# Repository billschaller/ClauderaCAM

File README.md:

# ClauderaCAM

Claude-drivable 2.5D heightmap CAM for the Makera Carvera Air.
STL relief → rough / semi / finish / cutout → **physical stock-simulation
verification** → live 3D viewer → .nc. Built from the exact code that cut
the brass Mango coin, then hardened by a 42-agent adversarial review whose
35 confirmed findings are each either fixed or a named check (see DESIGN.md
"2026-07-28: adversarial review & hardening"). A second lane mills PCBs
from KiCad gerbers through the same gate (see **The PCB lane** below).

## Setup

```sh
python3 -m venv .venv
.venv/bin/python -m pip install -e .          # pure-python (works everywhere)
.venv/bin/python -m pip install ./kernel      # optional Rust kernel (~10-50x
                                              # faster verify; needs cargo)
```

The two kernels are parity-locked (`tests/kernel_parity.py`): bit-exact
stock, epsilon-exact measurements. The Python one is the semantic reference.

## MCP (primary interface)

`.mcp.json` in this repo registers the server for Claude Code sessions
started here. From elsewhere:

```sh
claude mcp add --scope user clauderacam -- \
  <repo>/.venv/bin/python -m clauderacam.mcp_server
```

Tools: `load_job`, `generate`, `verify`, `preview`, `view` (opens the
job as a session in the live viewer, starting a server only if none is
running), `sessions` (lists open sessions). There is deliberately no
upload tool — .nc files reach the machine only by hand.

The viewer is a stage-aware, multi-session inspection app. One server
holds many sessions — one per open job file — and every process joins
it: the MCP, the CLI and any number of browser tabs land on the same
server via a discovery file, so a change Claude pushes appears in the
watching browser within a second. Sessions are keyed by job path, so
opening a file that is already open joins its session (that's the
collaboration model). In the browser: a session list with verdict
badges and a job-file picker (opening verifies in the background; the
browser never generates or edits — job changes are Claude's); per
session, the program's logical operations (recovered from the .nc bytes
themselves) as a selectable list with per-stage time estimates —
selecting one shows the simulated stock as it will exist after that
operation with the material that stage removes highlighted — plus a
stage-detail card (removed volume, tool contact, windowed chip load and
cutting power, each drawn as a utilization bar against its limit), the
tool library with the active stage's tool marked, and the full check
list. Claude runs the job; the viewer exists so a human — including a
CAM expert — can audit it. Each session offers a **download** of its
program — serving the exact bytes that were verified (stored at push
time; a later regenerate can never hand out unverified toolpaths under
a displayed PASS), with an explicit are-you-sure on anything not
cleared for metal. Downloading to a human hand is the Article VII
workflow: the file still reaches the machine only by that hand.

## CLI

```sh
.venv/bin/clauderacam all jobs/mango.toml       # generate + verify + preview
.venv/bin/clauderacam view jobs/mango.toml      # open in the live viewer at
                                                # :8323 (joins a running
                                                # server, else serves)
.venv/bin/clauderacam serve                     # empty viewer server; open
                                                # job files from the browser
```

## The rule

**Nothing goes to the machine without `verify` returning PASS.** The verifier
strictly parses the program (anything it cannot model — unknown tools, arcs,
modal G-less lines — is fatal, never skipped), carves every move into
virtual stock, and checks:

- *geometry (simulation facts):* rapids (lateral and descending), true
  per-move tool contact for every tool (footprint max vs move-start stock,
  limits calibrated to metal evidence), shank/holder clearance against
  standing stock, depth vs stock bottom, gouging below the target surface,
  surface completeness, cutout sever-through, the fixture keep-out zone,
  and the spindle-state dialect (M5 before M6, dwell after M3)
- *cutting physics (model verdicts, provenance-annotated in physics.py):*
  per-material sustained chip load and spindle power over 0.25s windows,
  rubbing (starvation feed), plunge rate, machine feed caps, a sustained-
  power heat proxy, and an enclosed-chip gumming proxy — materials carry
  specific cutting energy, chip-load floors and evacuation limits; tools
  carry flutes, flute length and shank geometry; the machine model is the
  Carvera Air's 200W / 13k RPM spindle

`tests/negative_suite.py` proves the gate can fail: 24 distilled hazards —
slams, stalls, rubbing, gumming, shank crashes, rapid plunges, arcs in
disguise — that must each be caught. `tests/stage_model.py` proves the
per-stage model tells the truth: stage snapshots partition the carve
bit-exactly and per-stage stats are measured, not inferred.

## Golden test

```sh
.venv/bin/python tests/golden_mango.py
```

Regenerates the mango job (`assets/mango-coin-d52.stl` — yes, that's a real
cat) and asserts byte-identical toolpaths against the G-code in
`tests/golden/` that cut the physical coin, then verifies the assembled
program. Run it after touching anything in `ops/`, `engine.py`, or
`heightmap.py`.

## Reference suite

```sh
.venv/bin/python tests/reference_suite.py
```

`assets/generate_references.py` synthesizes four deterministic shapes, each
paired with a job in `jobs/` that stresses a different hazard:

| job | exercises |
|---|---|
| `terraces` | layered-rough terracing on 0.22mm steps, simplify on flats, cutout with tabs |
| `dome` | 2mm flat rough (smaller tool = relaxed slope budget), two-ball finish chain, no cutout |
| `ripple` | 1mm ball finishing **directly** after rough — legal only because every slope is inside the engagement budget |
| `pocketfield` | graduated feature access by tool BODY (Ø7 down to 1.3mm slots) — honestly annotated: the shallow features are bottomed by the 2mm ball's contact circle; true tool exclusion awaits depth-stepped clearing |

Together with mango these cover the supported tool set: flat 3.175, flat 2.0,
ball 2.0, ball 1.0, plus twist drills for registration holes — the
geometries validated by cut metal. V-bits and tapered ball noses need a
conical offset model plus a real-world tip engagement limit, so they are
roadmap, not shipped guesses.

## Two-sided (pin-and-flip) jobs

One TOML with `[twosided]`, `[pins]` and per-side op lists describes a
coin machined on BOTH faces: side 1 cuts the front art plus a minimal
moat, then spot-faces and peck-drills registration holes through the
stock into the spoilboard — same setup, so the holes are coaxial by
construction. Flip the blank onto dowel pins (layout must be symmetric
under the configured flip axis — enforced), and side 2 cuts the back art
and the tabbed cutout. Two .nc programs come out; each verifies through
the same gate, and the back side is additionally checked against the
carried, flipped front stock: punch-through into the front art, sever
against the actual material bottom, a continuous tab bridge from coin to
skeleton, and pin keep-out. The cutout's `tab_top` is derived from the
carried front floor to hit a target `tab_bridge` thickness (hand-written
values are refused — the first cut coin's hand-picked tab_top made
0.24mm tabs that snapped too thin). `jobs/twoside-ref.toml` +
`tests/twosided_suite.py` are the executable spec, negatives included.

## The PCB lane

Gerbers + Excellon in, verified Carvera programs out: isolation-milled
PCBs through the same gate. A `[pcb]` TOML names a KiCad export
directory and parameterizes the operator's six-phase chain — cut traces
(0.2mm vee, a multi-pass ladder so gaps too wide for one pass and too
narrow for the clearing tool still come out copper-free) → clear copper
→ solder mask *(operator: squeegee + UV cure)* → silkscreen (455nm
laser onto the cured mask) → scrub mask off pads (spring tool) →
drills + edge cut. FlatCAM (a pinned headless
fork) runs as the **geometry engine only**: its per-phase output is
strictly parsed and re-emitted through `emit.py`, so every shipped byte
obeys the house dialect (the laser program has its own — one `M321`,
then a mandatory `G0 Z0` defocus, dose-ceilinged `M3 S`). Verification
never trusts the generator: gerbv rasterizes the same gerbers through
an unrelated parser lineage, and the gate measures the assembled
programs against those maps — iso containment *and* coverage, a
residual-copper law on the simulated carve (no bridging sliver survives
between what isolation reaches and what clearing owns — a loupe-found
incident), clearing margins, scrub laps inside pad copper, pad
scrubbability, thermal-relief spoke delivery, silk clearance and stroke
metrics, the exact Excellon hole schedule, cutout ride + tab census,
and true sheet stock simulation for the milling programs
(`guides/pcb-dfm-notes.md` translates the big fab houses' hand-solder
DFM rules into this milled lane's numbers). Double-sided boards compose
`[pcb]` + `[twosided]`: per-side phase tables, both machine frames
derived from the one Edge.Cuts, registration pins under the coin lane's
pins law, both-side annular-ring and flip-concentricity checks for
hand-soldered wire vias, and a side-2 scrub generator that laps
drilled pads annularly instead of driving the spring tip across open
holes. Board contracts — plus each board's assembly map, companion
sheet and machine-side tool pull-list — live in `boards/`, golden
assets in `tests/golden_pcb/`; the viewer opens a `[pcb]` job as one
session per
program, with 2D overlays for the non-carving stages and the
operator's run-sheet card. FlatCAM and gerbv are external optional
binaries (like the Rust kernel): the blessed goldens verify without
them and the suites skip loudly.

## The tool crib

`jobs/inventory.toml` is the machine's physical tool inventory. A job may
only use tools that match an entry — type, diameter, shank, flutes,
reach, quantity on hand — and refuses to **load** otherwise (Article XI).
Geometry in the crib is measured or catalog-sourced, never guessed; a
tool with an unknown dimension is absent, and the resulting refusal is
the feature.

## Project law

`CLAUDE.md` is the constitution: the verification gate, the golden-test
contract, and the incident-traced safety rules. Read it before contributing —
human or model.

## License & credits

MIT (see LICENSE). Vendors [three.js](https://threejs.org) r160 (MIT) for the
viewer. Named for Claude + Carvera: designed and written by
[Claude Code](https://claude.com/claude-code) working alongside a human
machinist, and proven by cutting real metal before it was ever a package.

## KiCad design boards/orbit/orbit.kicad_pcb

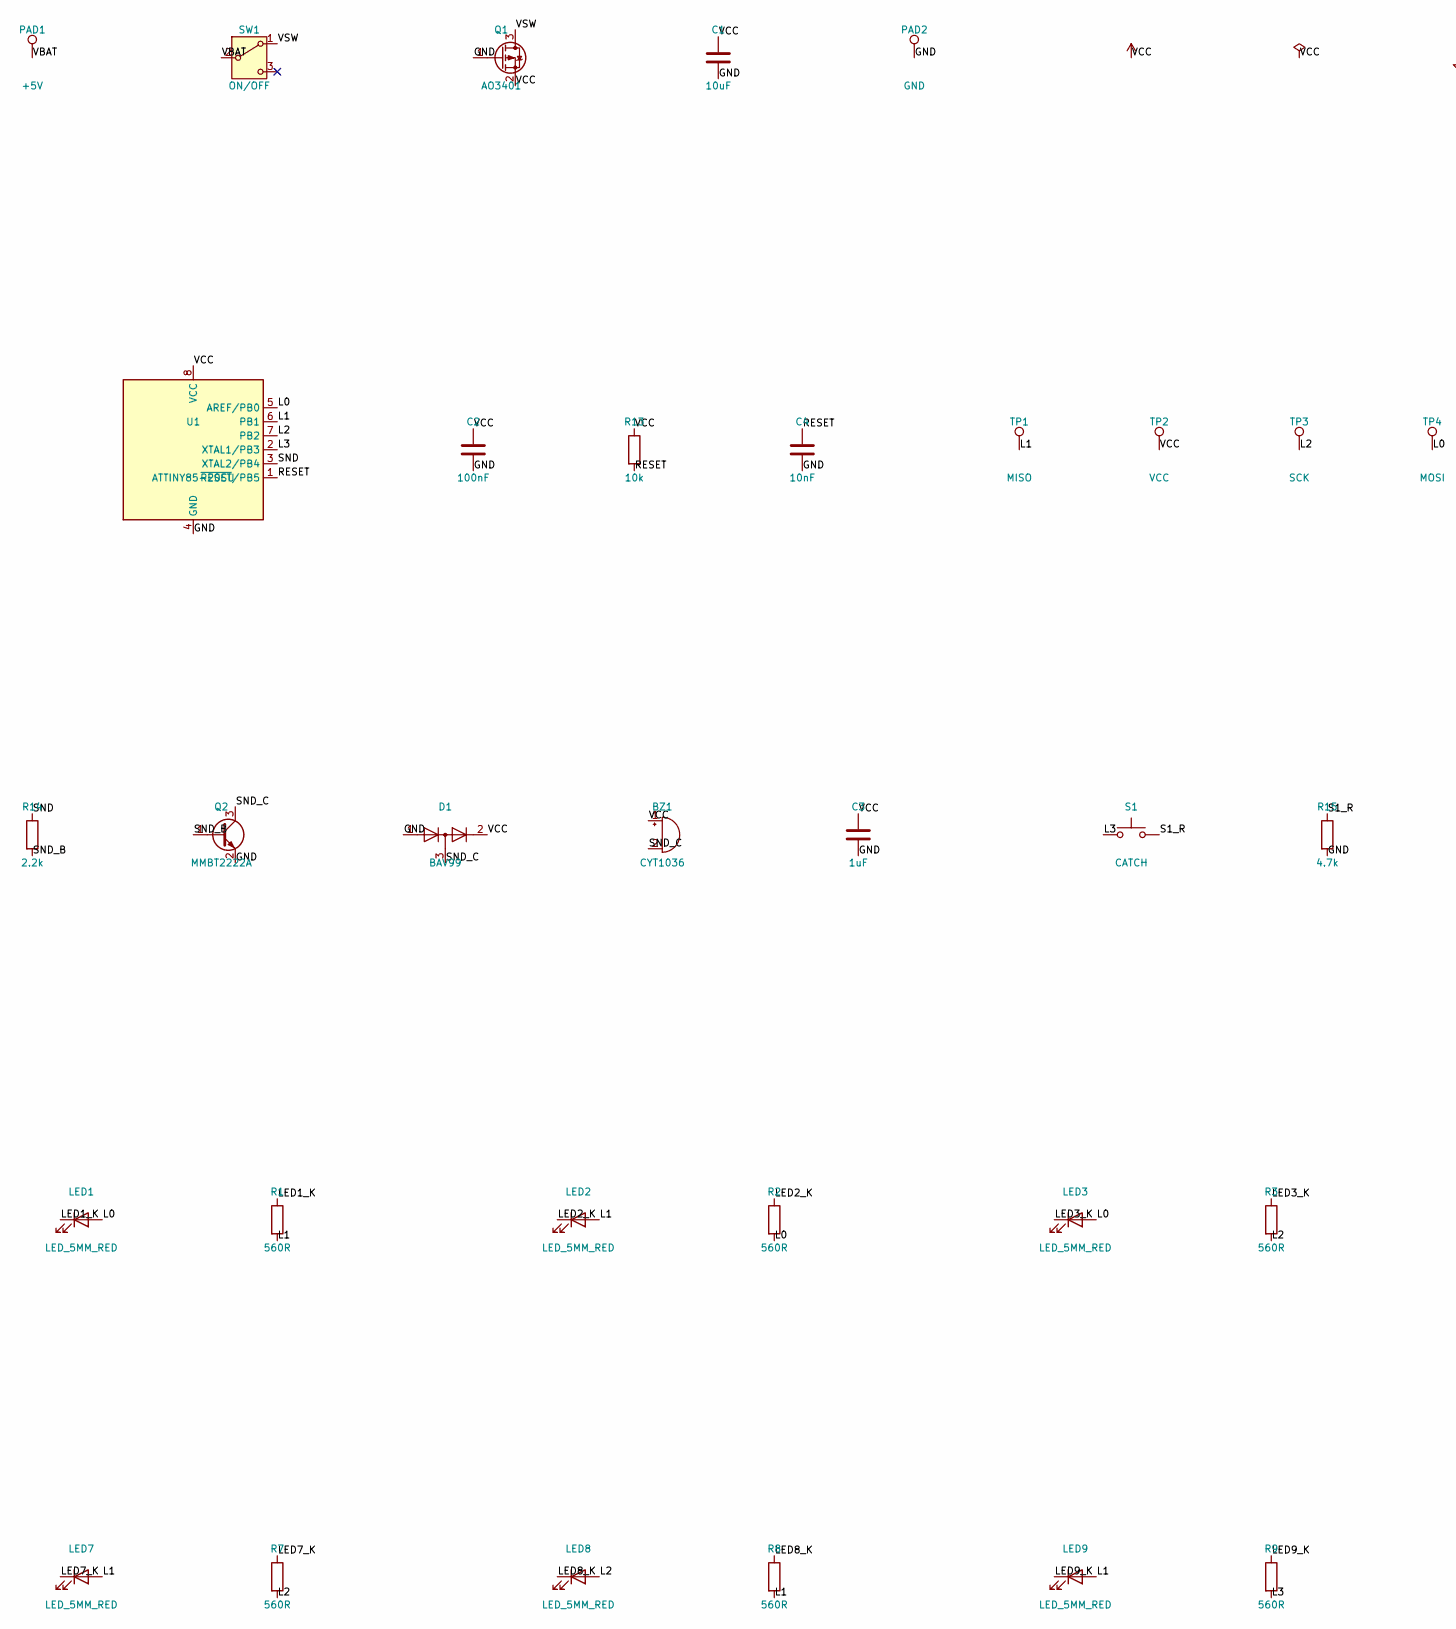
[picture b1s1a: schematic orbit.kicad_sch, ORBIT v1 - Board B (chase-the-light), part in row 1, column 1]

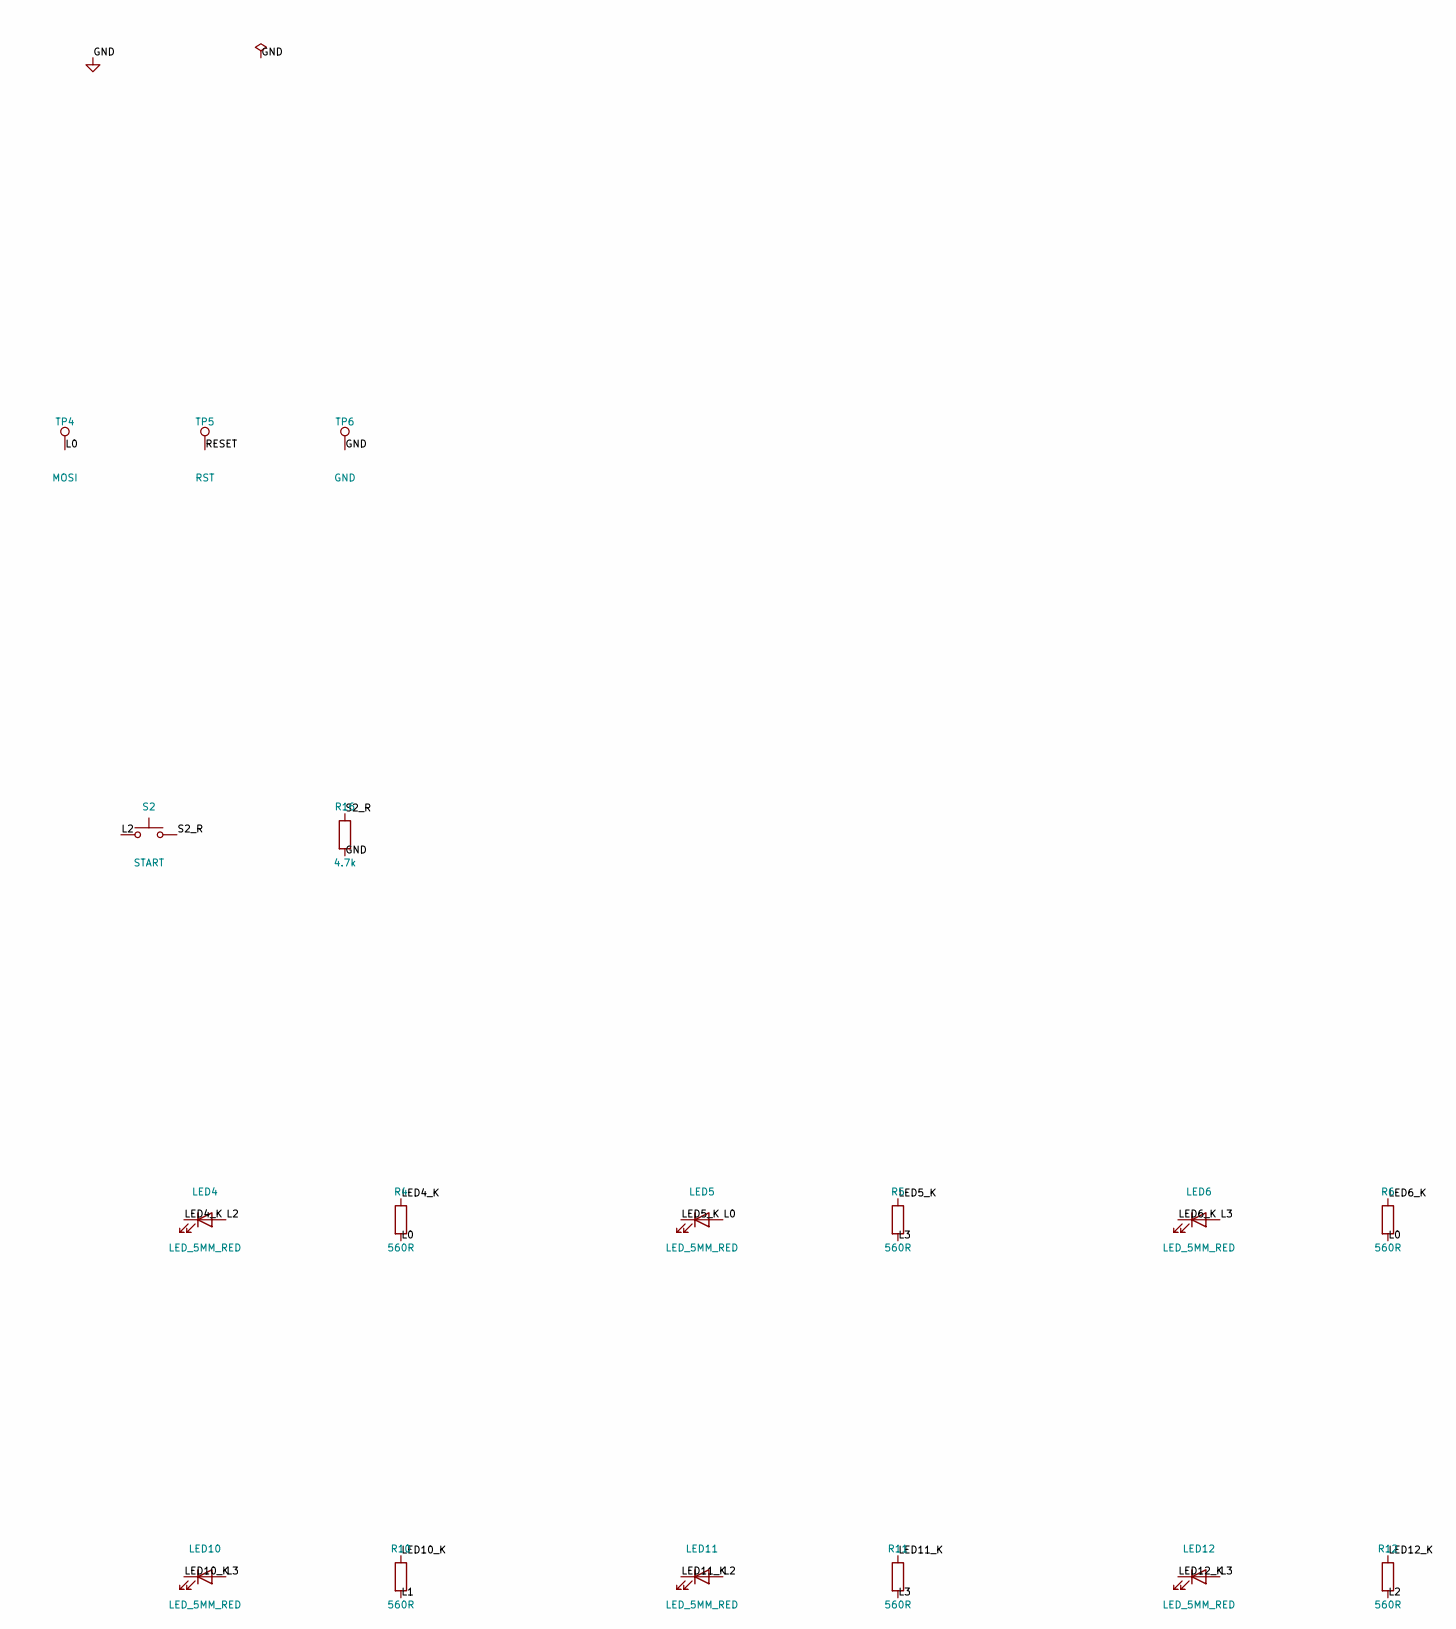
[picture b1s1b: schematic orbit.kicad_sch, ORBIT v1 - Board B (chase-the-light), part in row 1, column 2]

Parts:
BZ1: CYT1036; Buzzer_12x9.5RM7.6
C1: 10uF; C_0805_2012Metric_Pad1.18x1.45mm_HandSolder
C2: 100nF; C_0805_2012Metric_Pad1.18x1.45mm_HandSolder
C3: 1uF; C_0603_1608Metric_Pad1.08x0.95mm_HandSolder
C4: 10nF; C_1206_3216Metric_Pad1.33x1.80mm_HandSolder
D1: BAV99; SOT-23_Handsoldering
LED1, LED2, LED3, LED4, LED5, LED6, LED7, LED8, LED9, LED10, LED11, LED12: LED_5MM_RED; LED_D5.0mm
PAD1: +5V; WirePad_D3.6mm_Drill1.5mm
PAD2: GND; WirePad_D3.6mm_Drill1.5mm
Q1: AO3401; SOT-23_Handsoldering
Q2: MMBT2222A; SOT-23_Handsoldering
R1, R4, R7, R10: 560R; R_1206_3216Metric_Pad1.30x1.75mm_HandSolder
R2, R5, R8, R11: 560R; R_0805_2012Metric_Pad1.20x1.40mm_HandSolder
R3, R6, R9, R12: 560R; R_0603_1608Metric_Pad0.98x0.95mm_HandSolder
R13: 10k; R_0603_1608Metric_Pad0.98x0.95mm_HandSolder
R14: 2.2k; R_0805_2012Metric_Pad1.20x1.40mm_HandSolder
R15: 4.7k; R_1206_3216Metric_Pad1.30x1.75mm_HandSolder
R16: 4.7k; R_0603_1608Metric_Pad0.98x0.95mm_HandSolder
S1: CATCH; SW_PUSH_6mm
S2: START; SW_PUSH_6mm
SW1: ON/OFF; SW_Slide_SPDT_P4.86mm_D1.8mm
TP1: MISO; ISP_Pad_D1.8mm
TP2: VCC; ISP_Pad_D1.8mm
TP3: SCK; ISP_Pad_D1.8mm
TP4: MOSI; ISP_Pad_D1.8mm
TP5: RST; ISP_Pad_D1.8mm
TP6: GND; ISP_Pad_D1.8mm
U1: ATTINY85-20SU; SOIC-8_5.3x5.3mm_P1.27mm

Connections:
/L0: LED1.2 (A), LED3.2 (A), LED5.2 (A), R2.2, R4.2, R6.2, TP4.1, U1.5 (AREF/PB0)
/L1: LED2.2 (A), LED7.2 (A), LED9.2 (A), R1.2, R8.2, R10.2, TP1.1, U1.6 (PB1)
/L2: LED4.2 (A), LED8.2 (A), LED11.2 (A), R3.2, R7.2, R12.2, S2.1, TP3.1, U1.7 (PB2)
/L3: LED6.2 (A), LED10.2 (A), LED12.2 (A), R5.2, R9.2, R11.2, S1.1, U1.2 (XTAL1/PB3)
/LED1_K: LED1.1 (K), R1.1
/LED2_K: LED2.1 (K), R2.1
/LED3_K: LED3.1 (K), R3.1
/LED4_K: LED4.1 (K), R4.1
/LED5_K: LED5.1 (K), R5.1
/LED6_K: LED6.1 (K), R6.1
/LED7_K: LED7.1 (K), R7.1
/LED8_K: LED8.1 (K), R8.1
/LED9_K: LED9.1 (K), R9.1
/LED10_K: LED10.1 (K), R10.1
/LED11_K: LED11.1 (K), R11.1
/LED12_K: LED12.1 (K), R12.1
/RESET: C4.1, R13.2, TP5.1, U1.1 (~RESET/PB5)
/S1_R: R15.1, S1.2
/S2_R: R16.1, S2.2
/SND: R14.1, U1.3 (XTAL2/PB4)
/SND_B: Q2.1 (B), R14.2
/SND_C: BZ1.2 (-), D1.3 (K), Q2.3 (C)
/VBAT: PAD1.1, SW1.2 (B)
/VSW: Q1.3 (D), SW1.1 (A)
GND: C1.2, C2.2, C3.2, C4.2, D1.1 (K), PAD2.1, Q1.1 (G), Q2.2 (E), R15.2, R16.2, TP6.1, U1.4 (GND)
VCC: BZ1.1 (+), C1.1, C2.1, C3.1, D1.2 (A), Q1.2 (S), R13.1, TP2.1, U1.8 (VCC)

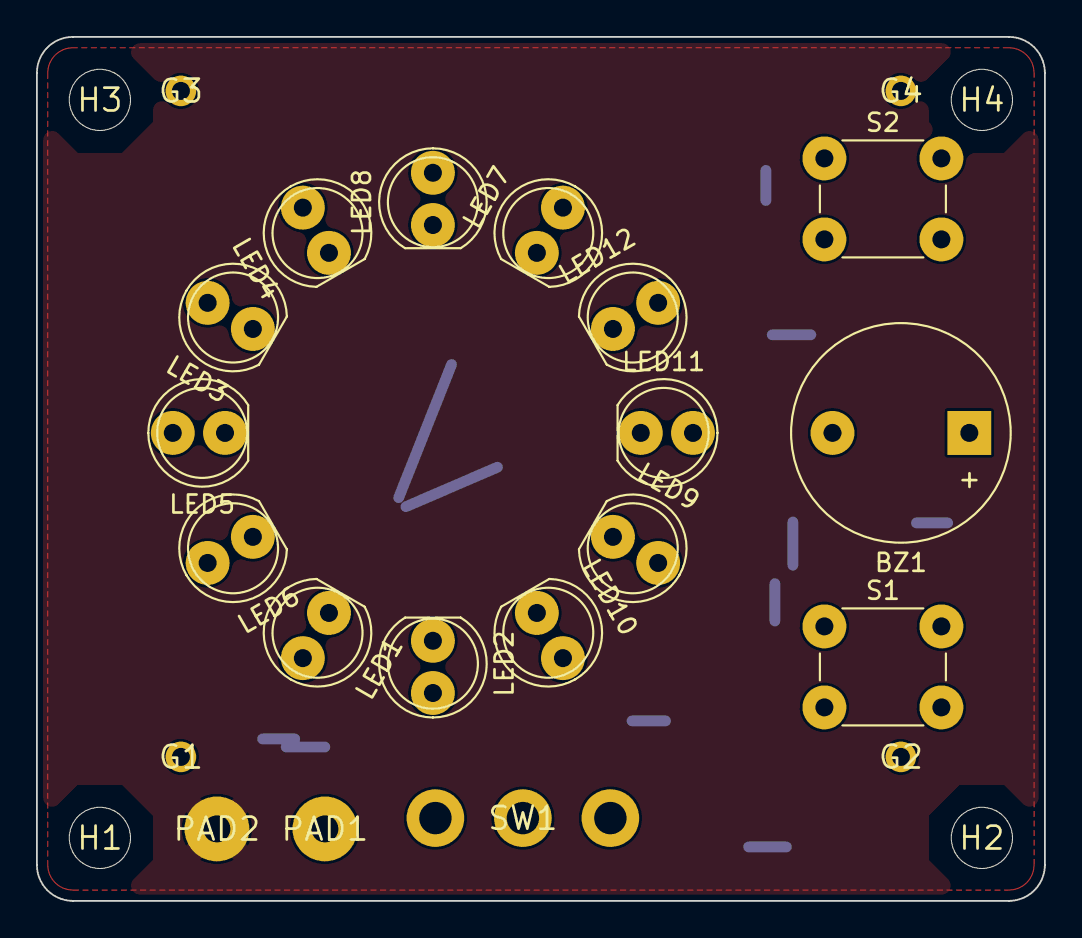
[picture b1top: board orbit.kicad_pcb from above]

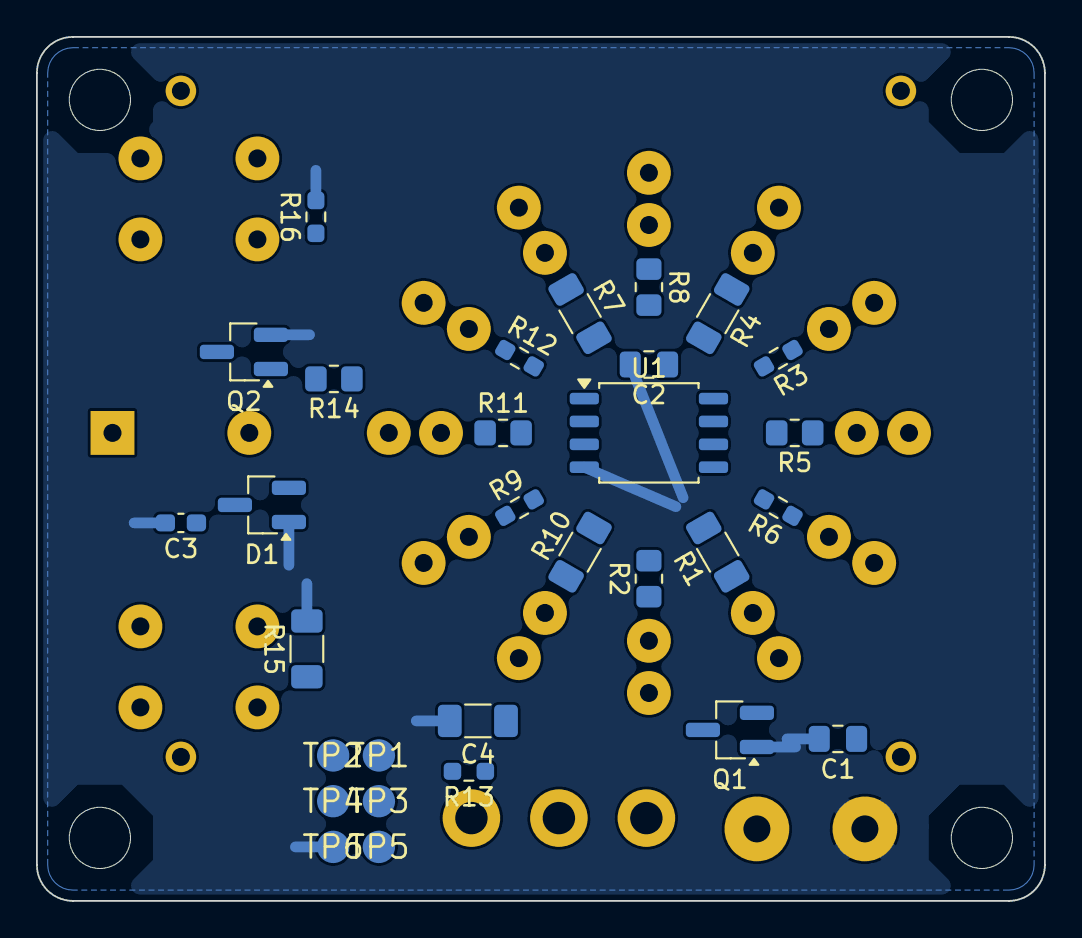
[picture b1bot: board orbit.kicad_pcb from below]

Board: 2 copper layers, 56.0 x 48.0 mm, 56 parts (30 on the bottom side), 26 nets.

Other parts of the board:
G1, G2, G3, G4: flip gauge; FlipGauge_D1.7mm_Drill1.0mm
H1, H2, H3, H4: MountingHole_3.4mm_NPTH

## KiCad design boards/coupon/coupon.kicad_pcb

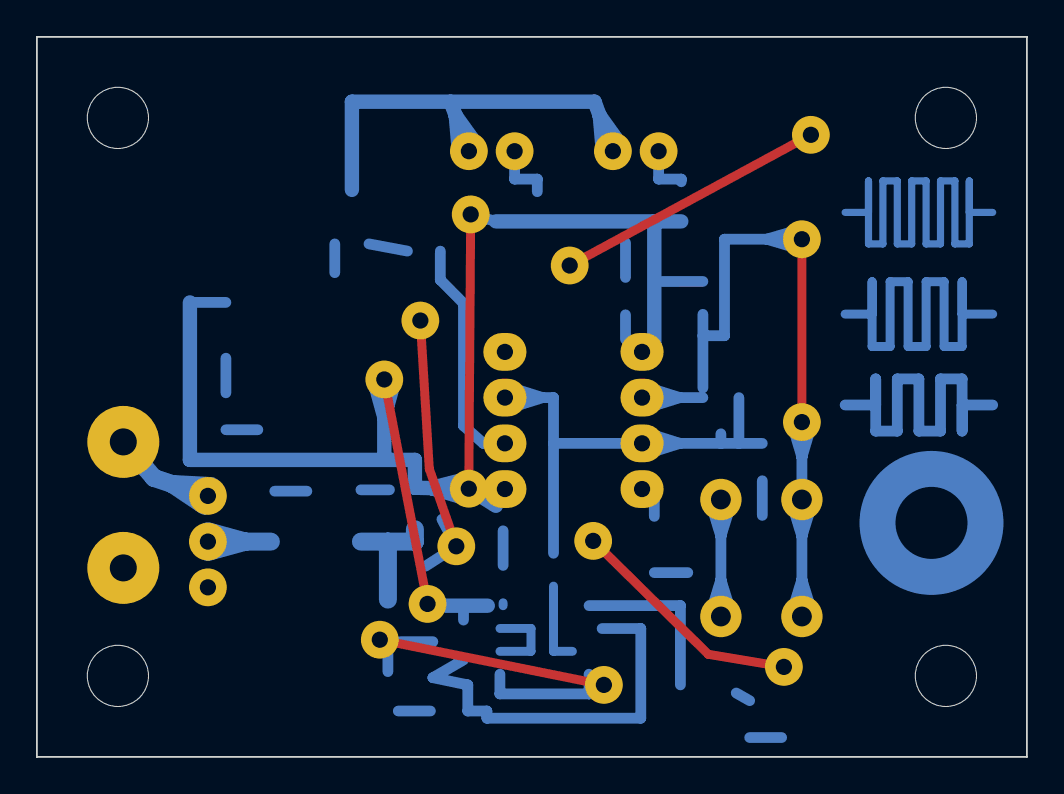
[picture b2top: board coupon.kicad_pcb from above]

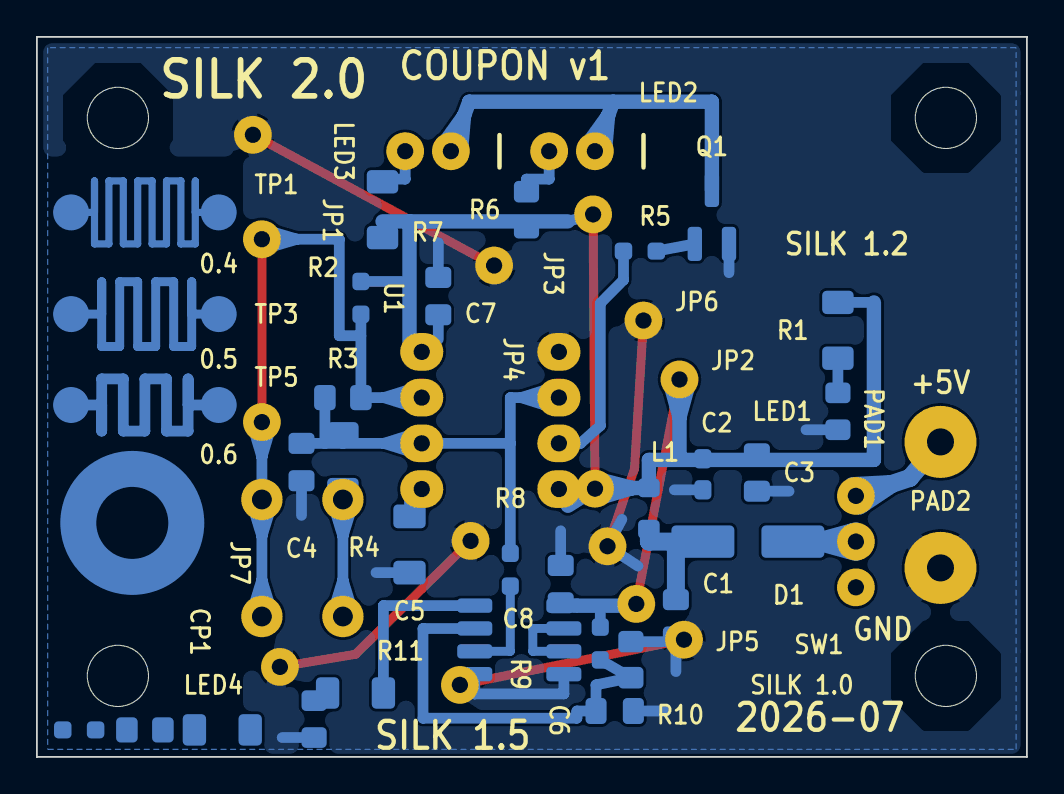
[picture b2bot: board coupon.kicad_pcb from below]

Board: 2 copper layers, 55.0 x 40.0 mm, 52 parts (34 on the bottom side), 23 nets.

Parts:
C1, C4: 10uF; C_0805_2012Metric_Pad1.18x1.45mm_HandSolder
C2: 1uF; C_0603_1608Metric_Pad1.08x0.95mm_HandSolder
C3, C6, C7, C8: 100nF; C_0805_2012Metric_Pad1.18x1.45mm_HandSolder
C5: 10nF; C_1206_3216Metric_Pad1.33x1.80mm_HandSolder
CP1: coupon; R_1206_3216Metric_Pad1.30x1.75mm_HandSolder
CP2: coupon; R_0805_2012Metric_Pad1.20x1.40mm_HandSolder
CP3: coupon; R_0603_1608Metric_Pad0.98x0.95mm_HandSolder
D1: SS14; D_SMA_Handsoldering
H1, H2, H3, H4: MountingHole_3.4mm_NPTH
JP1: wire 10.16mm; JumperWire_P10.16mm
JP2, JP5, JP6, JP7: wire 12.7mm; JumperWire_P12.7mm
JP3, JP4: wire 15.24mm; JumperWire_P15.24mm
L1: 10uH; L_0805_2012Metric_Pad1.05x1.20mm_HandSolder
LED1: LED_RED; LED_0805_2012Metric_Pad1.15x1.40mm_HandSolder
LED2, LED3: LED_5MM; LED_D5.0mm
LED4: LED_GRN; LED_0805_2012Metric_Pad1.15x1.40mm_HandSolder
PAD1: +5V; TestPoint_THTPad_D4.0mm_Drill2.0mm
PAD2: GND; TestPoint_THTPad_D4.0mm_Drill2.0mm
Q1: S8050; SOT-23_Handsoldering
R1: 1k; R_1206_3216Metric_Pad1.30x1.75mm_HandSolder
R2, R9: 10k; R_0603_1608Metric_Pad0.98x0.95mm_HandSolder
R3: 33k; R_0805_2012Metric_Pad1.20x1.40mm_HandSolder
R4: 6.8k; R_1206_3216Metric_Pad1.30x1.75mm_HandSolder
R5: 1k; R_0603_1608Metric_Pad0.98x0.95mm_HandSolder
R6: 330R; R_0805_2012Metric_Pad1.20x1.40mm_HandSolder
R7, R11: 330R; R_1206_3216Metric_Pad1.30x1.75mm_HandSolder
R8: 100k; R_0603_1608Metric_Pad0.98x0.95mm_HandSolder
R10: 10k; R_0805_2012Metric_Pad1.20x1.40mm_HandSolder
S2: SW_Push; SW_PUSH_6mm
SW1: SW_SPDT; SW_Slide_SS12D00_HandMill
TP1, TP2, TP3, TP4, TP5, TP6: TestPoint; TestPoint_Pad_D2.0mm
U1: NE555P; DIP-8_W7.62mm_Socket
U2: LM358; SOIC-8_3.9x4.9mm_P1.27mm

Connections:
/BLINK: R5.1, U1.3
/LADDER_040: TP1.1, TP2.1
/LADDER_050: TP3.1, TP4.1
/LADDER_060: TP5.1, TP6.1
/LEDK: LED2.1, LED3.1, Q1.3
/N_CV: C5.1, U1.5
/N_DISCH: JP1.1, JP1.2, R2.2, R3.1, S2.1, U1.7
/N_KICK: R4.1, S2.2
/N_LED1: LED1.2, R1.2
/N_LED2A: LED2.2, R6.2
/N_LED3A: LED3.2, R7.2
/N_LED4A: LED4.2, R11.2
/N_Q1B: Q1.1, R5.2
/N_U2AIN: R8.2, U2.3
/N_U2AOUT: R11.1, U2.1
/N_U2BFB: U2.6, U2.7
/TRIG_THR: C4.1, R3.2, R4.2, R8.1, U1.2, U1.6
/VF: C1.1, D1.1, L1.1
/VHALF: C6.1, R9.2, R10.1, U2.2
/VIN: PAD1.1, SW1.1
/VIN_SW: D1.2, SW1.2
GND: C1.2, C2.2, C3.2, C4.2, C5.2, C6.2, C7.2, C8.2, JP4.1, JP4.2, JP5.1, JP5.2, JP6.1, JP6.2, JP7.1, JP7.2, LED1.1, LED4.1, PAD2.1, Q1.2, R10.2, U1.1, U2.4, U2.5
VCC: C2.1, C3.1, C7.1, C8.1, JP2.1, JP2.2, JP3.1, JP3.2, L1.2, R1.1, R2.1, R6.1, R7.1, R9.1, U1.4, U1.8, U2.8

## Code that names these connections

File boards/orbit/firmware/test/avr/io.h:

/* test/avr/io.h -- host mock of the ATtiny85 I/O space.
 * Registers become ordinary variables so the host test can watch every write
 * the firmware makes to the port pins.  Bit numbers are the real ones. */
#ifndef MOCK_AVR_IO_H
#define MOCK_AVR_IO_H
#include <stdint.h>

uint8_t DDRB, PORTB, PINB, SREG;
uint8_t TCCR0A, TCCR0B, OCR0A, TIFR, TIMSK;
uint8_t GIMSK, GIFR, PCMSK, CLKPR, PRR;
uint8_t ADMUX, ADCSRA, ADCH, DIDR0;

#define PB0 0
#define PB1 1
#define PB2 2
#define PB3 3
#define PB4 4
#define PB5 5

#define WGM01 1
#define CS00  0
#define CS01  1
#define OCF0A 4
#define OCIE0A 4
#define PCIE  5
#define PCIF  5
#define CLKPCE 7
#define PRTIM1 3
#define PRUSI  1
#define PRADC  0
#define ADLAR 5
#define ADEN  7
#define ADSC  6
#define ADPS2 2

#endif
